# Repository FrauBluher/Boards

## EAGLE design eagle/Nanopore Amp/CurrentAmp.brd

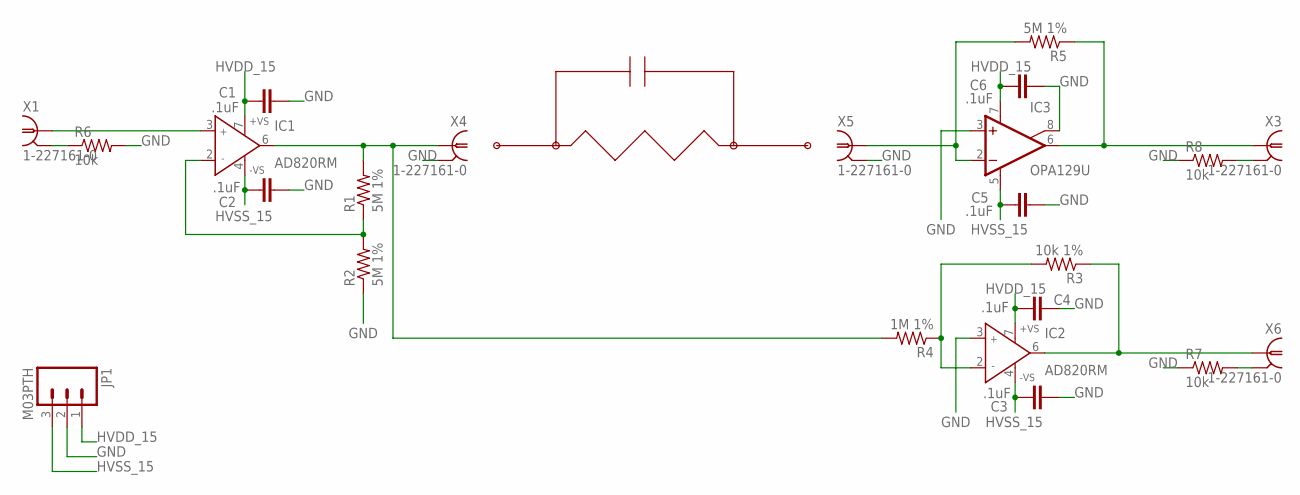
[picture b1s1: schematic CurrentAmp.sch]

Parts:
C1, C2, C3, C4, C5, C6: .1uF; 0805
IC1, IC2: AD820RM; MSOP08
IC3: OPA129U; SO08
JP1: M03PTH; 1X03
R1, R2, R5: 5M 1%; 0805
R3: 10k 1%; 0805
R4: 1M 1%; 0805
R6, R7, R8: 10k; 0805
X1, X3, X4, X5, X6: 1-227161-0; AMP_227161

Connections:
GND: C1.2, C2.2, C3.2, C4.2, C5.2, C6.2, IC2.3 (IN+), IC3.3 (+IN), IC3.8 (SUBS), JP1.2, R2.1, R6.2, R7.1, R8.1, X4.2, X5.2
HVDD_15: C1.1, C4.1, C6.1, IC1.7 (+VS), IC2.7 (+VS), IC3.7 (V+), JP1.1
HVSS_15: C2.1, C3.1, C5.1, IC1.4 (-VS), IC2.4 (-VS), IC3.5 (V-), JP1.3
unnamed: IC1.2 (IN-), R1.1, R2.2
unnamed: IC1.3 (IN+), X1.1
unnamed: IC2.2 (IN-), R3.2, R4.1
unnamed: IC2.6 (OUT), R3.1, X6.1
unnamed: IC1.6 (OUT), R1.2, R4.2, X4.1
unnamed: IC3.6 (OUT), R5.1, X3.1
unnamed: IC3.2 (-IN), R5.2, X5.1
unnamed: R6.1, X1.2
unnamed: R8.2, X3.2
unnamed: R7.2, X6.2

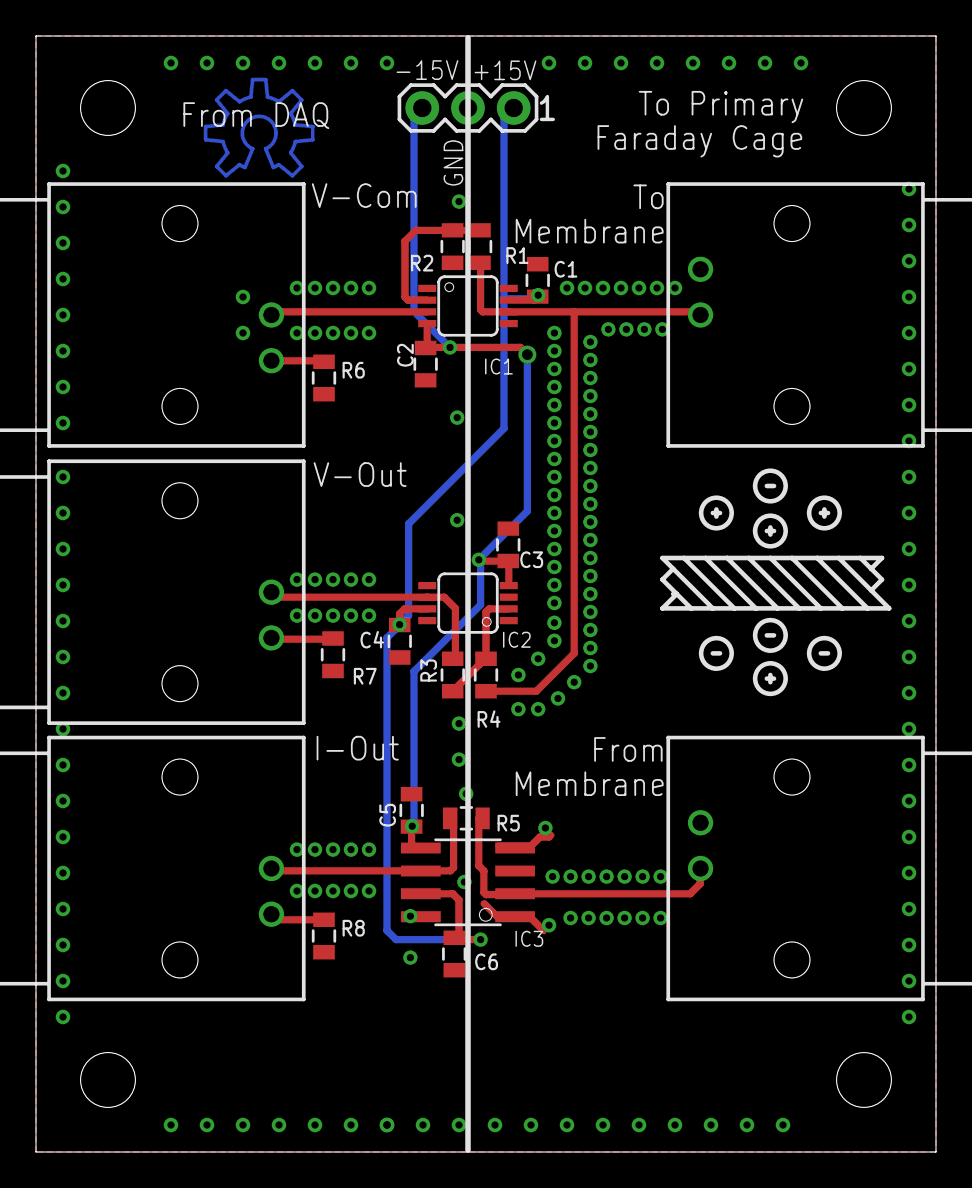
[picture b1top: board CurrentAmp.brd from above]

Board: 2 copper layers, 50.0 x 62.0 mm, 27 parts (0 on the bottom side), 13 nets.

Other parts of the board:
E$1, E$2, E$3, E$4: STAND-OFF-TIGHT

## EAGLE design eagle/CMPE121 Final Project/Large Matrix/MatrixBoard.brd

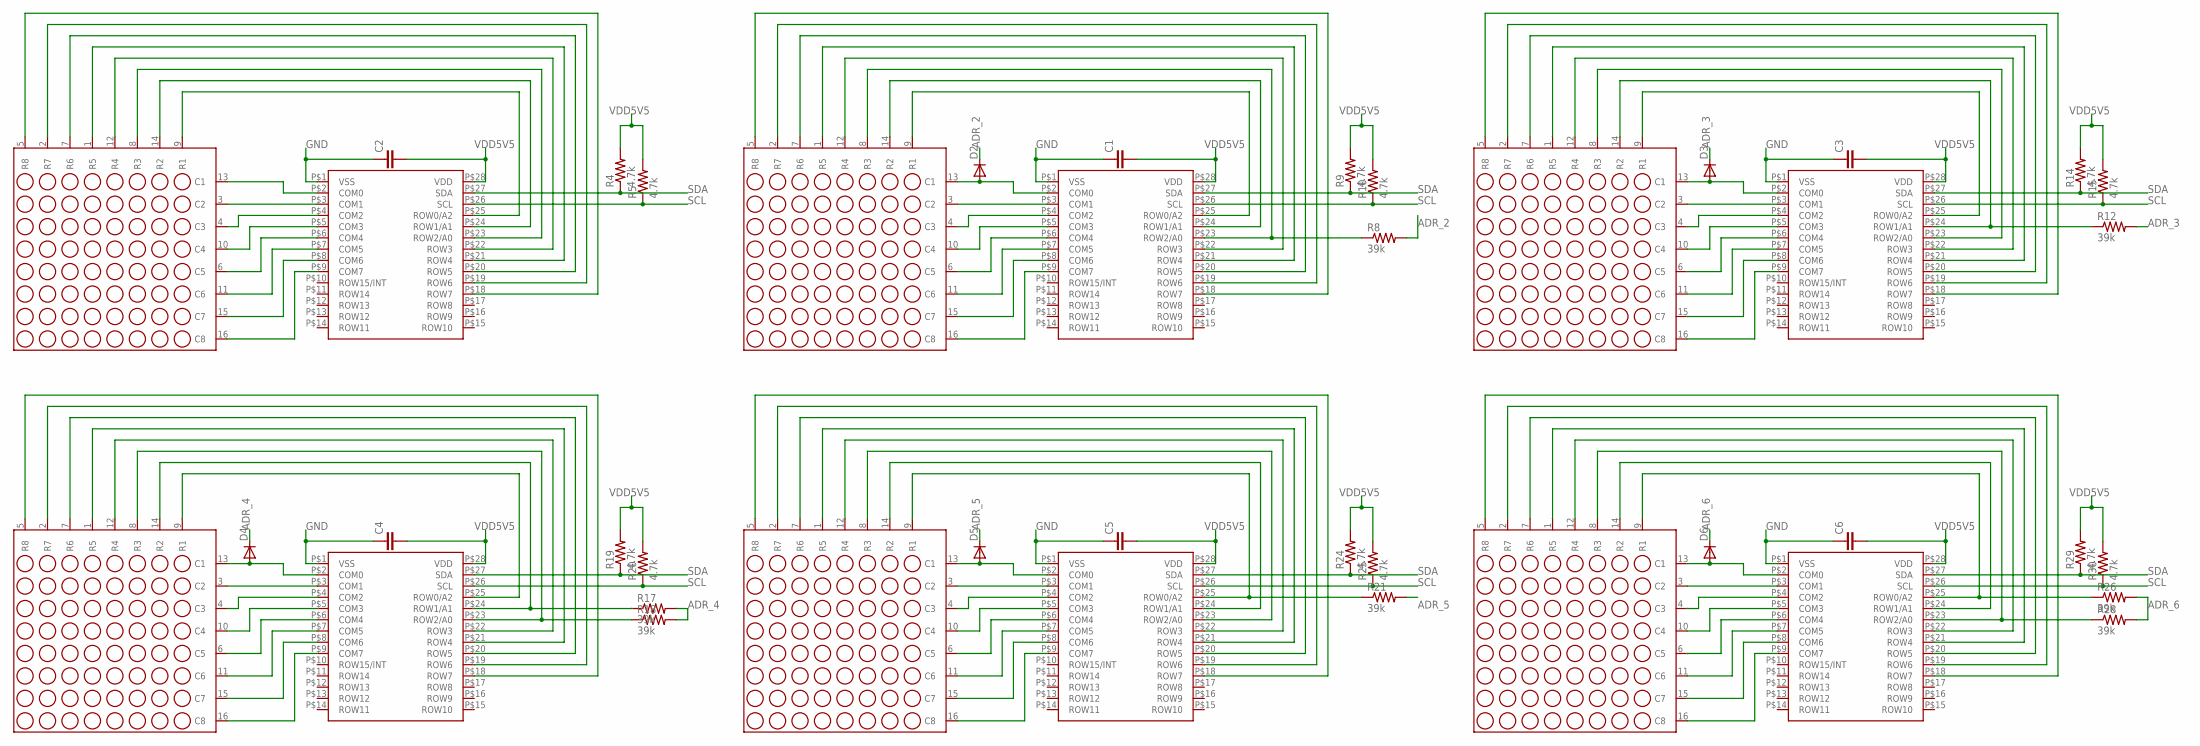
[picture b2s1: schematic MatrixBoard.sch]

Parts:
C1, C2, C3, C4, C5, C6: CAP0805; 0805
D2, D3, D4, D5, D6: DIODESMA; SMA-DIODE
R4, R5, R9, R10, R14, R15, R19, R20, R24, R25, R29, R30: 4.7k; 0805
R8, R12, R17, R18, R21, R26, R28: 39k; 0805
U$2, U$4, U$6, U$8, U$10, U$12: A-788BS
U$3, U$5, U$7, U$9, U$11, U$13: HT16K33; SOIC28-W

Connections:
ADR_2: D2.C, R8.2
ADR_3: D3.C, R12.2
ADR_4: D4.C, R17.2, R18.2
ADR_5: D5.C, R21.2
ADR_6: D6.C, R26.2, R28.2
GND: C1.1, C2.1, C3.1, C4.1, C5.1, C6.1, U$3.P$1 (VSS), U$5.P$1 (VSS), U$7.P$1 (VSS), U$9.P$1 (VSS), U$11.P$1 (VSS), U$13.P$1 (VSS)
unnamed: U$2.13 (C1), U$3.P$2 (COM0)
unnamed: U$2.3 (C2), U$3.P$3 (COM1)
unnamed: U$2.4 (C3), U$3.P$4 (COM2)
unnamed: U$2.10 (C4), U$3.P$5 (COM3)
unnamed: U$2.6 (C5), U$3.P$6 (COM4)
unnamed: U$2.11 (C6), U$3.P$7 (COM5)
unnamed: U$2.15 (C7), U$3.P$8 (COM6)
unnamed: U$2.16 (C8), U$3.P$9 (COM7)
unnamed: D2.A, U$4.13 (C1), U$5.P$2 (COM0)
unnamed: U$4.3 (C2), U$5.P$3 (COM1)
unnamed: U$4.4 (C3), U$5.P$4 (COM2)
unnamed: U$4.10 (C4), U$5.P$5 (COM3)
unnamed: U$2.9 (R1), U$3.P$25 (ROW0/A2)
unnamed: U$2.14 (R2), U$3.P$24 (ROW1/A1)
unnamed: U$2.8 (R3), U$3.P$23 (ROW2/A0)
unnamed: U$2.12 (R4), U$3.P$22 (ROW3)
unnamed: U$2.1 (R5), U$3.P$21 (ROW4)
unnamed: U$2.7 (R6), U$3.P$20 (ROW5)
unnamed: U$2.2 (R7), U$3.P$19 (ROW6)
unnamed: U$2.5 (R8), U$3.P$18 (ROW7)
unnamed: U$4.6 (C5), U$5.P$6 (COM4)
unnamed: U$4.11 (C6), U$5.P$7 (COM5)
unnamed: U$4.15 (C7), U$5.P$8 (COM6)
unnamed: U$4.16 (C8), U$5.P$9 (COM7)
unnamed: U$4.9 (R1), U$5.P$25 (ROW0/A2)
unnamed: U$4.14 (R2), U$5.P$24 (ROW1/A1)
unnamed: R8.1, U$4.8 (R3), U$5.P$23 (ROW2/A0)
unnamed: U$4.12 (R4), U$5.P$22 (ROW3)
unnamed: U$4.1 (R5), U$5.P$21 (ROW4)
unnamed: U$4.7 (R6), U$5.P$20 (ROW5)
unnamed: U$4.2 (R7), U$5.P$19 (ROW6)
unnamed: U$4.5 (R8), U$5.P$18 (ROW7)
unnamed: D3.A, U$6.13 (C1), U$7.P$2 (COM0)
unnamed: U$6.3 (C2), U$7.P$3 (COM1)
unnamed: U$6.4 (C3), U$7.P$4 (COM2)
unnamed: U$6.10 (C4), U$7.P$5 (COM3)
unnamed: U$6.6 (C5), U$7.P$6 (COM4)
unnamed: U$6.11 (C6), U$7.P$7 (COM5)
unnamed: U$6.15 (C7), U$7.P$8 (COM6)
unnamed: U$6.16 (C8), U$7.P$9 (COM7)
unnamed: U$6.9 (R1), U$7.P$25 (ROW0/A2)
unnamed: R12.1, U$6.14 (R2), U$7.P$24 (ROW1/A1)
unnamed: U$6.8 (R3), U$7.P$23 (ROW2/A0)
unnamed: U$6.12 (R4), U$7.P$22 (ROW3)
unnamed: U$6.1 (R5), U$7.P$21 (ROW4)
unnamed: U$6.7 (R6), U$7.P$20 (ROW5)
unnamed: U$6.2 (R7), U$7.P$19 (ROW6)
unnamed: U$6.5 (R8), U$7.P$18 (ROW7)
unnamed: D4.A, U$12.13 (C1), U$13.P$2 (COM0)
unnamed: U$12.3 (C2), U$13.P$3 (COM1)
unnamed: U$12.4 (C3), U$13.P$4 (COM2)
unnamed: U$12.10 (C4), U$13.P$5 (COM3)
unnamed: U$12.6 (C5), U$13.P$6 (COM4)
unnamed: U$12.11 (C6), U$13.P$7 (COM5)
unnamed: U$12.15 (C7), U$13.P$8 (COM6)
unnamed: U$12.16 (C8), U$13.P$9 (COM7)
unnamed: U$12.9 (R1), U$13.P$25 (ROW0/A2)
unnamed: R17.1, U$12.14 (R2), U$13.P$24 (ROW1/A1)
unnamed: R18.1, U$12.8 (R3), U$13.P$23 (ROW2/A0)
unnamed: U$12.12 (R4), U$13.P$22 (ROW3)
unnamed: U$12.1 (R5), U$13.P$21 (ROW4)
unnamed: U$12.7 (R6), U$13.P$20 (ROW5)
unnamed: U$12.2 (R7), U$13.P$19 (ROW6)
unnamed: U$12.5 (R8), U$13.P$18 (ROW7)
unnamed: D5.A, U$10.13 (C1), U$11.P$2 (COM0)
unnamed: U$10.3 (C2), U$11.P$3 (COM1)
unnamed: U$10.4 (C3), U$11.P$4 (COM2)
unnamed: U$10.10 (C4), U$11.P$5 (COM3)
unnamed: U$10.6 (C5), U$11.P$6 (COM4)
unnamed: U$10.11 (C6), U$11.P$7 (COM5)
unnamed: U$10.15 (C7), U$11.P$8 (COM6)
unnamed: U$10.16 (C8), U$11.P$9 (COM7)
unnamed: R21.1, U$10.9 (R1), U$11.P$25 (ROW0/A2)
unnamed: U$10.14 (R2), U$11.P$24 (ROW1/A1)
unnamed: U$10.8 (R3), U$11.P$23 (ROW2/A0)
unnamed: U$10.12 (R4), U$11.P$22 (ROW3)
unnamed: U$10.1 (R5), U$11.P$21 (ROW4)
unnamed: U$10.7 (R6), U$11.P$20 (ROW5)
unnamed: U$10.2 (R7), U$11.P$19 (ROW6)
unnamed: U$10.5 (R8), U$11.P$18 (ROW7)
unnamed: D6.A, U$8.13 (C1), U$9.P$2 (COM0)
unnamed: U$8.3 (C2), U$9.P$3 (COM1)
unnamed: U$8.4 (C3), U$9.P$4 (COM2)
unnamed: U$8.10 (C4), U$9.P$5 (COM3)
unnamed: U$8.6 (C5), U$9.P$6 (COM4)
unnamed: U$8.11 (C6), U$9.P$7 (COM5)
unnamed: U$8.15 (C7), U$9.P$8 (COM6)
unnamed: U$8.16 (C8), U$9.P$9 (COM7)
unnamed: R26.1, U$8.9 (R1), U$9.P$25 (ROW0/A2)
unnamed: U$8.14 (R2), U$9.P$24 (ROW1/A1)
unnamed: R28.1, U$8.8 (R3), U$9.P$23 (ROW2/A0)
unnamed: U$8.12 (R4), U$9.P$22 (ROW3)
unnamed: U$8.1 (R5), U$9.P$21 (ROW4)
unnamed: U$8.7 (R6), U$9.P$20 (ROW5)
unnamed: U$8.2 (R7), U$9.P$19 (ROW6)
unnamed: U$8.5 (R8), U$9.P$18 (ROW7)
SCL: R5.1, R10.1, R15.1, R20.1, R25.1, R30.1, U$3.P$26 (SCL), U$5.P$26 (SCL), U$7.P$26 (SCL), U$9.P$26 (SCL), U$11.P$26 (SCL), U$13.P$26 (SCL)
SDA: R4.1, R9.1, R14.1, R19.1, R24.1, R29.1, U$3.P$27 (SDA), U$5.P$27 (SDA), U$7.P$27 (SDA), U$9.P$27 (SDA), U$11.P$27 (SDA), U$13.P$27 (SDA)
VDD5V5: C1.2, C2.2, C3.2, C4.2, C5.2, C6.2, R4.2, R5.2, R9.2, R10.2, R14.2, R15.2, R19.2, R20.2, R24.2, R25.2, R29.2, R30.2, U$3.P$28 (VDD), U$5.P$28 (VDD), U$7.P$28 (VDD), U$9.P$28 (VDD), U$11.P$28 (VDD), U$13.P$28 (VDD)

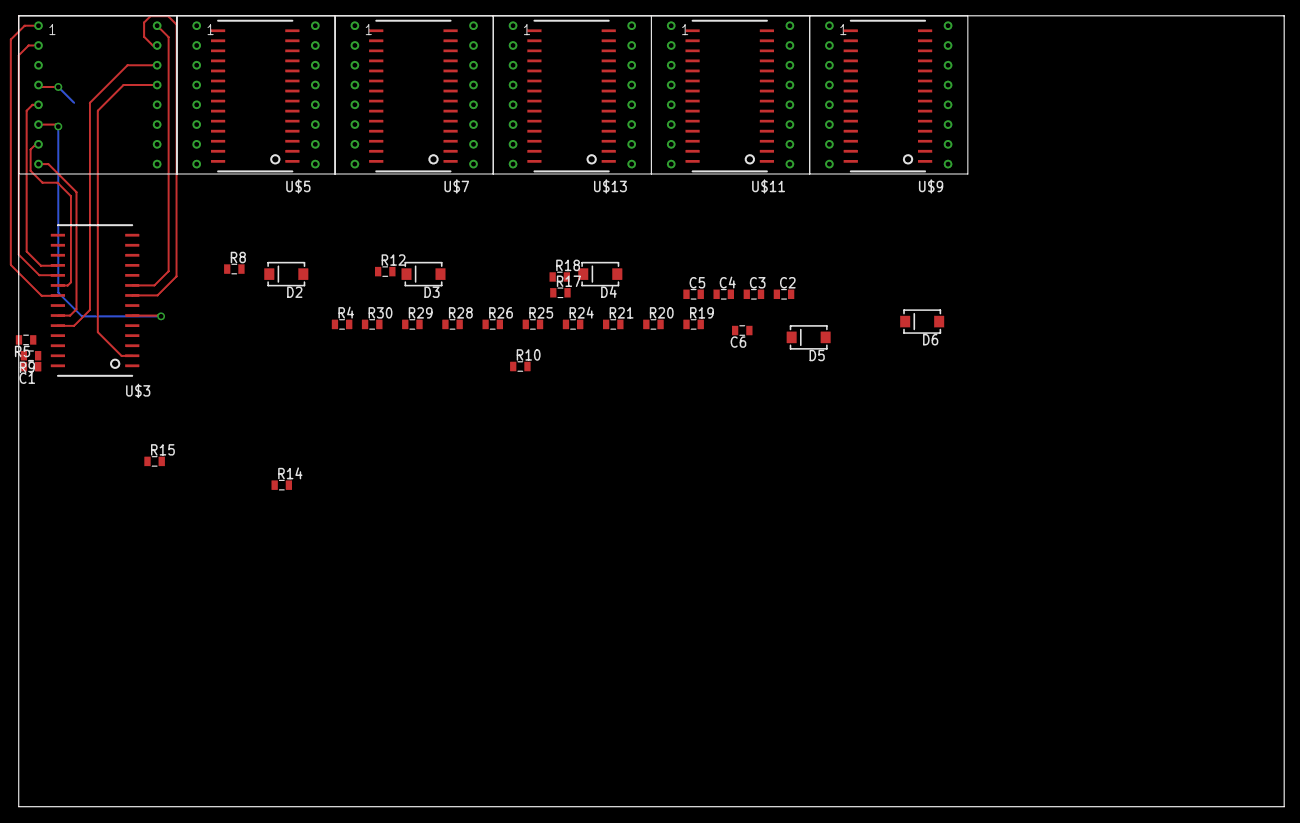
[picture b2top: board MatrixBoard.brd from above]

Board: 2 copper layers, 160.0 x 100.0 mm, 42 parts (0 on the bottom side), 105 nets.

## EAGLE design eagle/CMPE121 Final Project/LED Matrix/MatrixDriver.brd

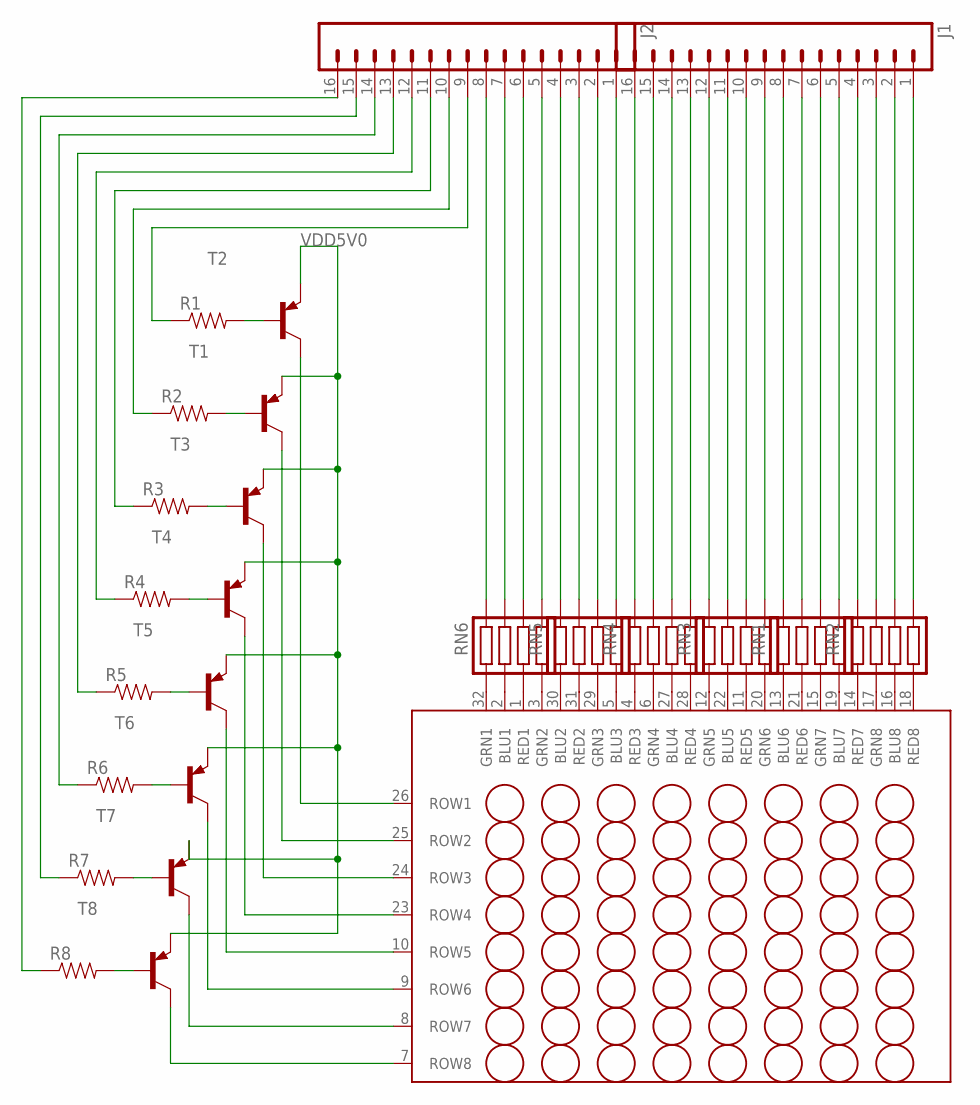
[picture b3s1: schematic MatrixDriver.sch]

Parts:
J1, J2: M16DUAL_ROW; 2X8
R1, R2, R3, R4, R5, R6, R7, R8: RESISTOR0805-RES; 0805
RN1, RN2, RN3, RN4, RN5, RN6: RESISTOR_ARRAY-4; EXB-38V271JV
T1, T2, T3, T4, T5, T6, T7, T8: 2N3906-PNP-TO92-EBC; TO92-EBC
U$1: BL-M23B88RGB-11; 8X8RGBMATRIX

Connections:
unnamed: T2.C, U$1.26 (ROW1)
unnamed: T1.C, U$1.25 (ROW2)
unnamed: T3.C, U$1.24 (ROW3)
unnamed: T4.C, U$1.23 (ROW4)
unnamed: T5.C, U$1.10 (ROW5)
unnamed: T6.C, U$1.9 (ROW6)
unnamed: T7.C, U$1.8 (ROW7)
unnamed: T8.C, U$1.7 (ROW8)
unnamed: RN1.P$5 (5), U$1.19 (BLU7)
unnamed: RN1.P$6 (6), U$1.15 (GRN7)
unnamed: RN1.P$7 (7), U$1.21 (RED6)
unnamed: RN1.P$8 (8), U$1.13 (BLU6)
unnamed: RN2.P$5 (5), U$1.18 (RED8)
unnamed: RN2.P$6 (6), U$1.16 (BLU8)
unnamed: RN2.P$7 (7), U$1.17 (GRN8)
unnamed: RN2.P$8 (8), U$1.14 (RED7)
unnamed: RN3.P$5 (5), U$1.20 (GRN6)
unnamed: RN3.P$6 (6), U$1.11 (RED5)
unnamed: RN3.P$7 (7), U$1.22 (BLU5)
unnamed: RN3.P$8 (8), U$1.12 (GRN5)
unnamed: RN4.P$5 (5), U$1.28 (RED4)
unnamed: RN4.P$6 (6), U$1.27 (BLU4)
unnamed: RN4.P$7 (7), U$1.6 (GRN4)
unnamed: RN4.P$8 (8), U$1.4 (RED3)
unnamed: RN5.P$5 (5), U$1.5 (BLU3)
unnamed: RN5.P$6 (6), U$1.29 (GRN3)
unnamed: RN5.P$7 (7), U$1.31 (RED2)
unnamed: RN5.P$8 (8), U$1.30 (BLU2)
unnamed: RN6.P$5 (5), U$1.3 (GRN2)
unnamed: RN6.P$6 (6), U$1.1 (RED1)
unnamed: RN6.P$7 (7), U$1.2 (BLU1)
unnamed: RN6.P$8 (8), U$1.32 (GRN1)
unnamed: J1.13, RN4.P$4 (4)
unnamed: J1.14, RN4.P$3 (3)
unnamed: J1.15, RN4.P$2 (2)
unnamed: J1.16, RN4.P$1 (1)
unnamed: J1.9, RN3.P$4 (4)
unnamed: J1.10, RN3.P$3 (3)
unnamed: J1.11, RN3.P$2 (2)
unnamed: J1.12, RN3.P$1 (1)
unnamed: J1.5, RN1.P$4 (4)
unnamed: J1.6, RN1.P$3 (3)
unnamed: J1.7, RN1.P$2 (2)
unnamed: J1.8, RN1.P$1 (1)
unnamed: J1.1, RN2.P$4 (4)
unnamed: J1.2, RN2.P$3 (3)
unnamed: J1.3, RN2.P$2 (2)
unnamed: J1.4, RN2.P$1 (1)
unnamed: J2.5, RN6.P$4 (4)
unnamed: J2.6, RN6.P$3 (3)
unnamed: J2.7, RN6.P$2 (2)
unnamed: J2.8, RN6.P$1 (1)
unnamed: J2.1, RN5.P$4 (4)
unnamed: J2.2, RN5.P$3 (3)
unnamed: J2.3, RN5.P$2 (2)
unnamed: J2.4, RN5.P$1 (1)
unnamed: J2.9, R1.1
unnamed: J2.10, R2.1
unnamed: J2.11, R3.1
unnamed: J2.12, R4.1
unnamed: J2.13, R5.1
unnamed: J2.14, R6.1
unnamed: J2.15, R7.1
unnamed: J2.16, R8.1
ROW1: R1.2, T2.B
ROW2: R2.2, T1.B
ROW3: R3.2, T3.B
ROW4: R4.2, T4.B
ROW5: R5.2, T5.B
ROW6: R6.2, T6.B
ROW7: R7.2, T7.B
ROW8: R8.2, T8.B
VDD5V0: T1.E, T2.E, T3.E, T4.E, T5.E, T6.E, T7.E, T8.E

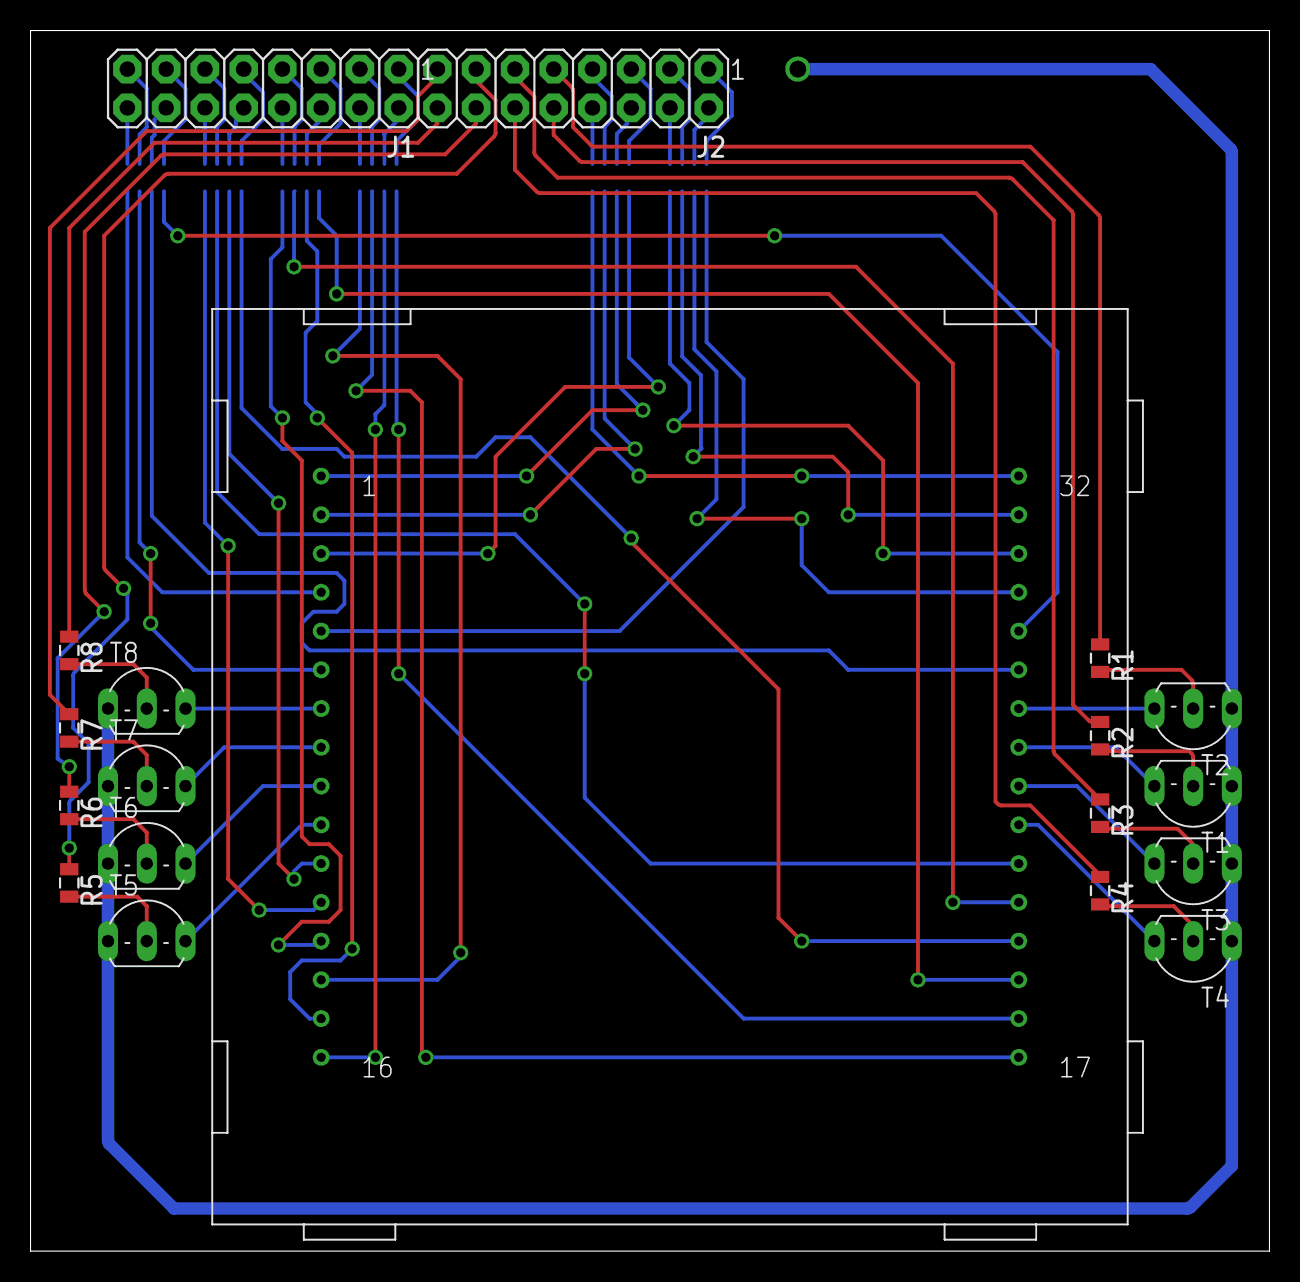
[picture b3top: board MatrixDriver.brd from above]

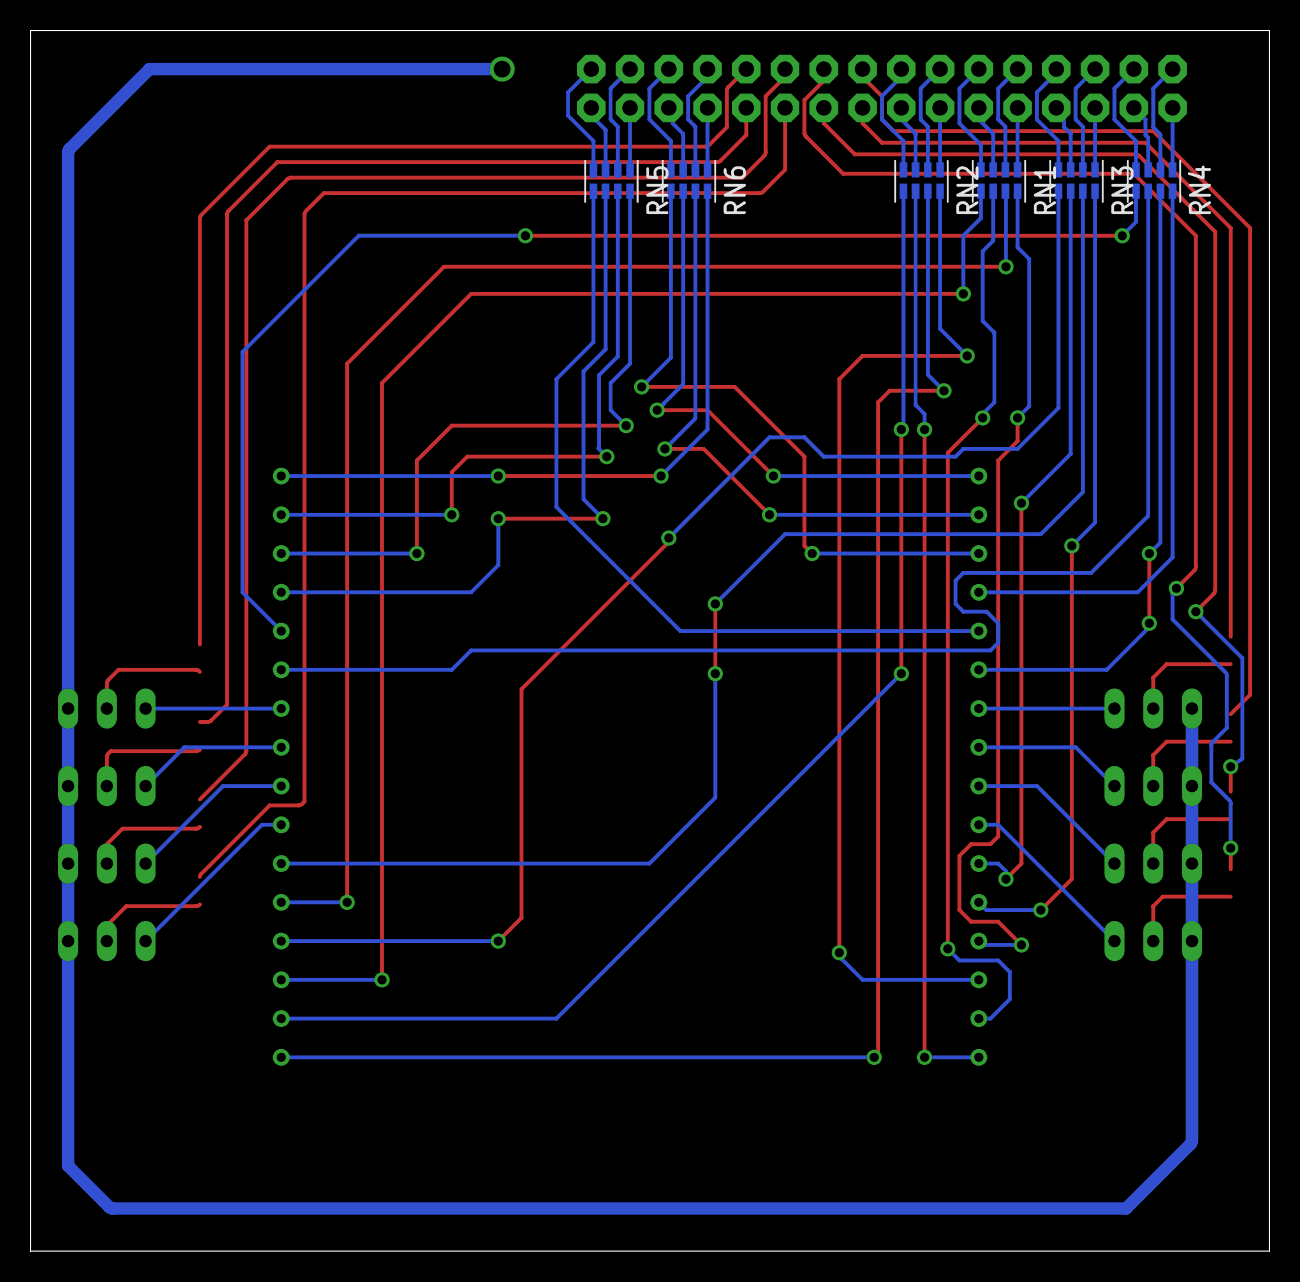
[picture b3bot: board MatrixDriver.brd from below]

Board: 2 copper layers, 81.2 x 80.0 mm, 25 parts (6 on the bottom side), 73 nets.

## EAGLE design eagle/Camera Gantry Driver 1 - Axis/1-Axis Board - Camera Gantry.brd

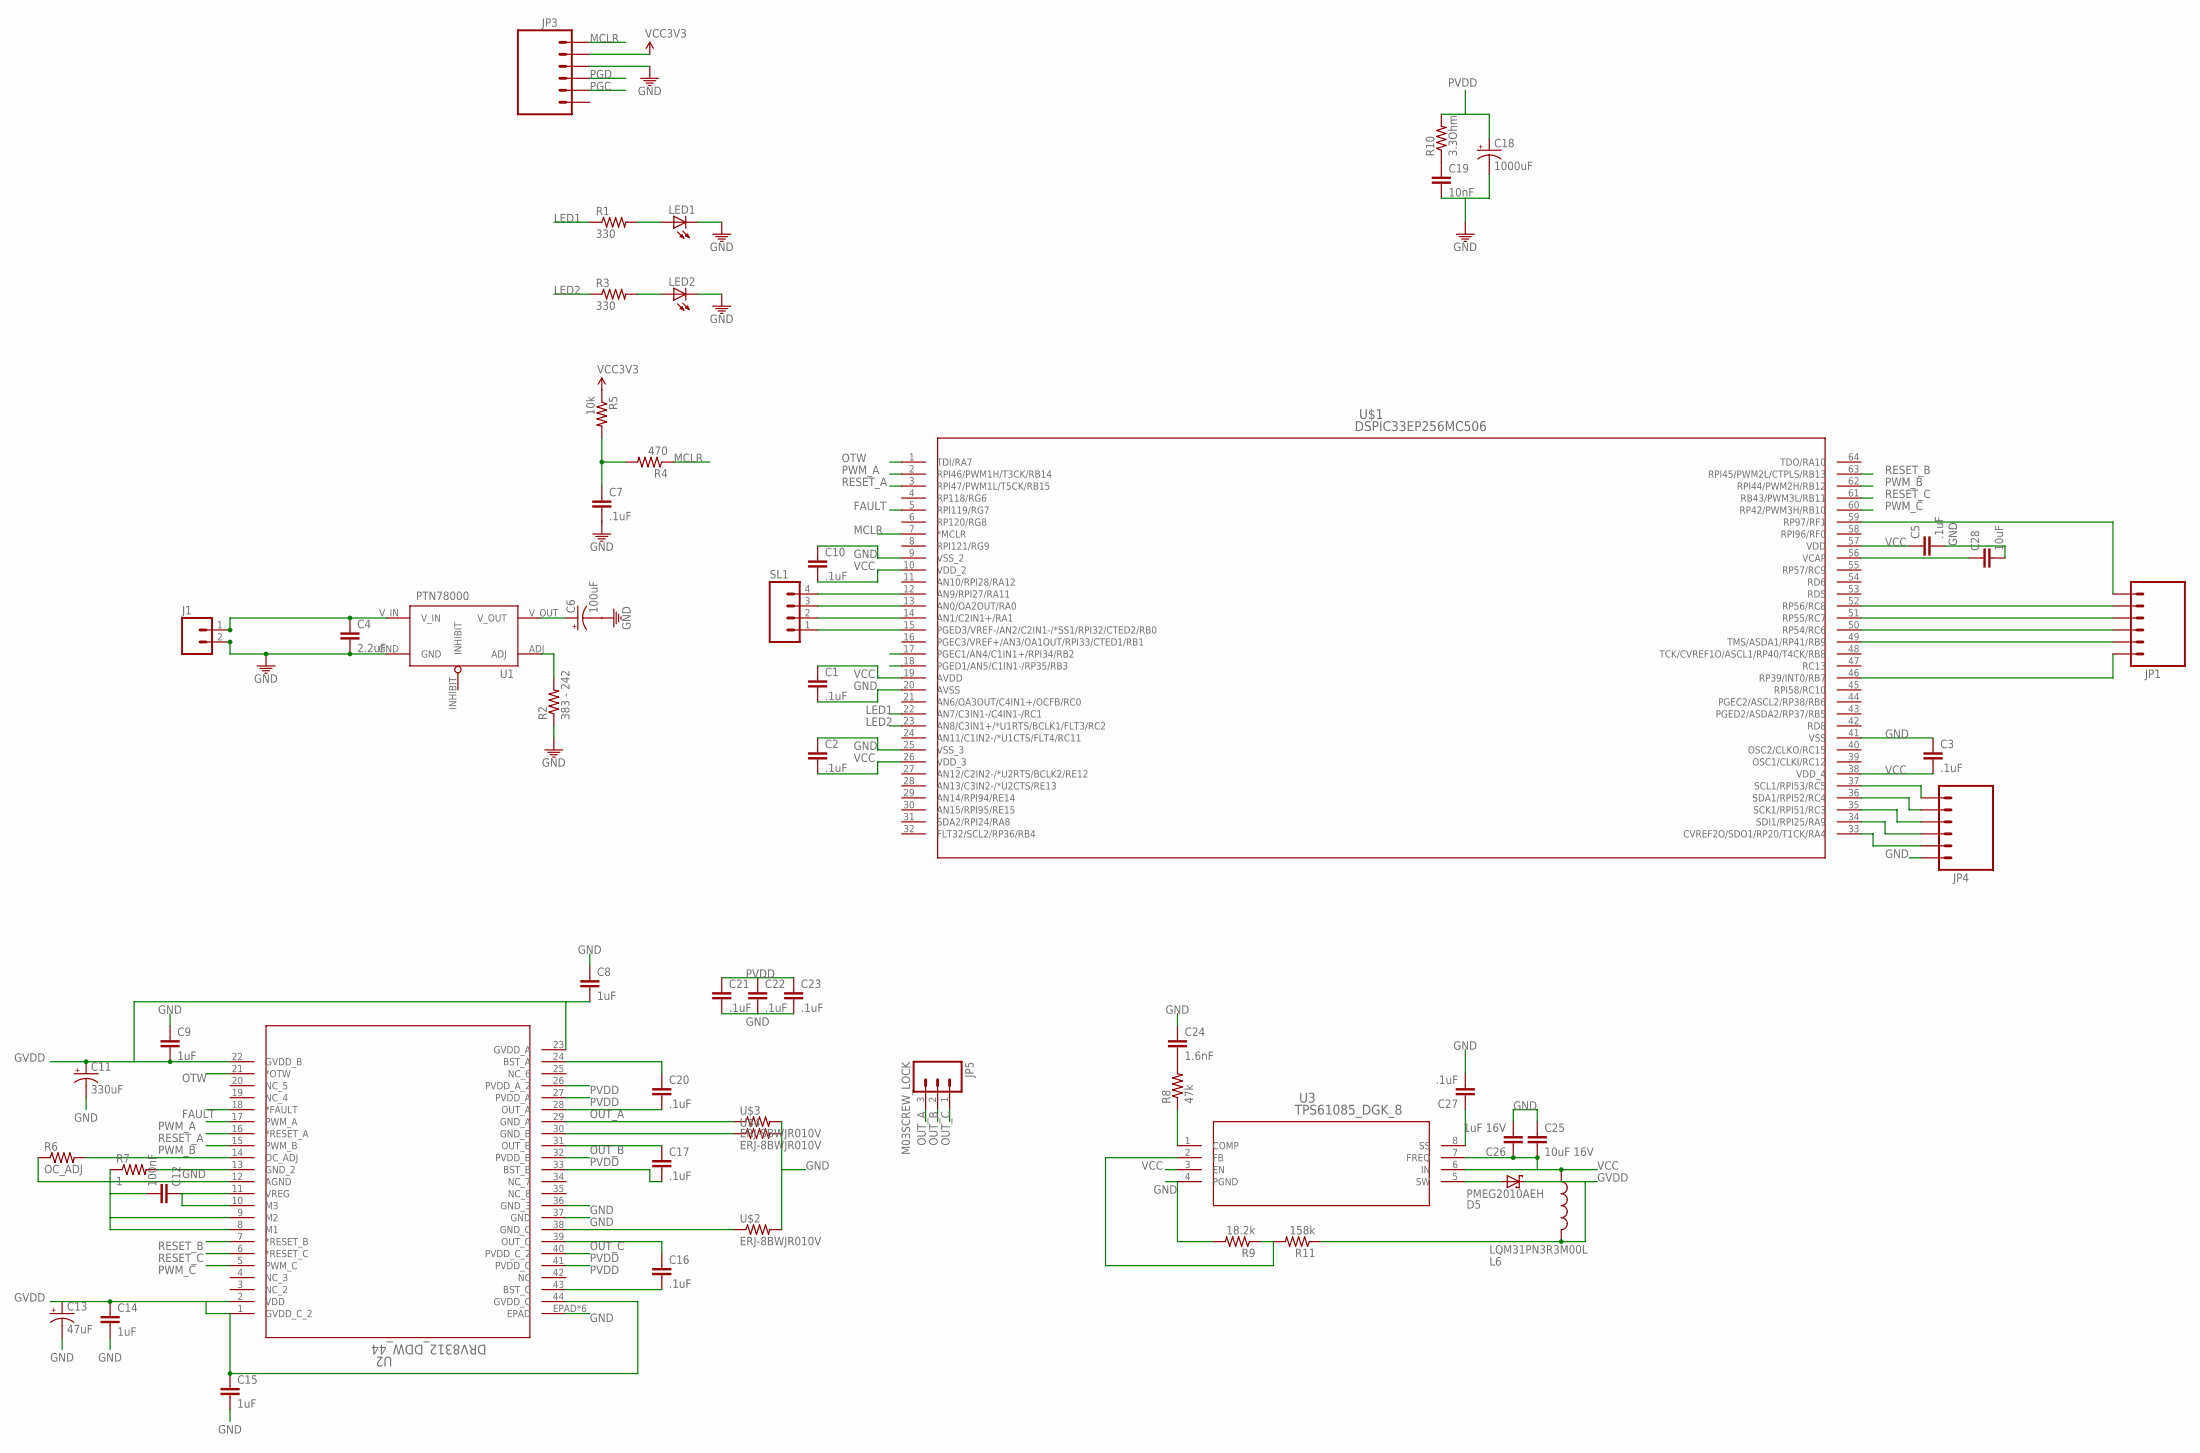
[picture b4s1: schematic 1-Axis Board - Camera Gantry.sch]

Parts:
C1, C2, C3, C5, C7, C10, C16, C17, C20, C21, C22, C23, C27: .1uF; 0805
C4: 2.2uF; 1206
C6: 100uF; CPOL-RADIAL-100UF-25V
C8, C9, C14, C15: 1uF; 0805
C11: 330uF; CPOL-RADIAL-1000UF-25V
C12: 100nF; 0805
C13: 47uF; CPOL-RADIAL-1000UF-25V
C18: 1000uF; CPOL-RADIAL-1000UF-25V
C19: 10nF; 0805
C24: 1.6nF; 0805
C25: 10uF 16V; 1206
C26: 1uF 16V; 0805
C28: 10uF; 1206
D5: PMEG2010AEH; SOD-123
J1: M023.5MM-NO_SILK; SCREWTERMINAL-3.5MM-2-NS
JP1, JP3, JP4: M06LOCK; 1X06_LOCK
JP5: M03SCREW_LOCK; SCREWTERMINAL-3.5MM-3_LOCK.007S
L6: LQM31PN3R3M00L; 1206
LED1, LED2: LED1206; LED-1206
R1, R3: 330; 0805
R2: 383 - 242; 0805
R4: 470; 0805
R5: 10k; 0805
R6: OC_ADJ; 0805
R7: 1; 0805
R8: 47k; 0805
R9: 18.2k; 0805
R10: 3.3Ohm; 0805
R11: 158k; 0805
SL1: M04LOCK; 1X04_LOCK
U1: PTN78000
U2: DRV8312_DDW_44; DDW44_8P26X4P31
U3: TPS61085_DGK_8; DGK8
U$1: DSPIC33EP256MC506; QFP64-10X10MC
U$2, U$3, U$4: ERJ-8BWJR010V; 1206

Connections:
FAULT: U2.18 (*FAULT), U$1.5 (RPI119/RG7)
GND: C1.2, C2.1, C3.1, C4.2, C5.2, C6.2 (-), C7.2, C8.1, C9.1, C10.1, C11.2 (-), C13.2 (-), C14.2, C15.2, C18.2 (-), C19.2, C21.2, C22.2, C23.2, C24.1, C25.1, C26.2, C27.2, C28.2, J1.2 (1), JP3.3, JP4.1, LED1.C, LED2.C, R2.1, R7.2, R9.2, U1.GND, U2.13 (GND_2), U2.36 (GND_3), U2.37 (GND), U2.EPAD, U2.P$1 (EPAD), U2.P$2 (EPAD), U2.P$3 (EPAD), U2.P$7 (EPAD), U2.P$8 (EPAD), U3.4 (PGND), U$1.9 (VSS_2), U$1.20 (AVSS), U$1.25 (VSS_3), U$1.41 (VSS), U$2.2, U$3.2, U$4.2
GVDD: C8.2, C9.2, C11.1 (+), C13.1 (+), C14.1, C15.1, D5.C, L6.2, R11.1, U2.1 (GVDD_C_2), U2.2 (VDD), U2.22 (GVDD_B), U2.23 (GVDD_A), U2.44 (GVDD_C)
LED1: R1.1, U$1.22 (AN7/C3IN1-/C4IN1-/RC1)
LED2: R3.1, U$1.23 (AN8/C3IN1+/*U1RTS/BCLK1/FLT3/RC2)
MCLR: JP3.1, R4.1, U$1.7 (*MCLR)
unnamed: LED1.A, R1.2
unnamed: C7.1, R4.2, R5.2
unnamed: LED2.A, R3.2
unnamed: U2.38 (GND_C), U$2.1
unnamed: U2.29 (GND_A), U$3.1
unnamed: R2.2, U1.ADJ
unnamed: U2.30 (GND_B), U$4.1
unnamed: C27.1, U3.8 (SS)
unnamed: R8.1, U3.1 (COMP)
unnamed: C24.2, R8.2
unnamed: C19.1, R10.1
unnamed: C28.1, U$1.56 (VCAP)
unnamed: D5.A, U3.5 (SW)
unnamed: R9.1, R11.2, U3.2 (FB)
unnamed: C16.2, U2.43 (BST_C)
unnamed: JP1.1, U$1.46 (RP39/INT0/RB7)
unnamed: JP1.2, U$1.49 (TMS/ASDA1/RP41/RB9)
unnamed: JP1.3, U$1.50 (RP54/RC6)
unnamed: JP1.5, U$1.52 (RP56/RC8)
unnamed: JP1.6, U$1.59 (RP97/RF1)
unnamed: C17.2, U2.33 (BST_B)
unnamed: JP1.4, U$1.51 (RP55/RC7)
unnamed: JP4.4, U$1.35 (SCK1/RPI51/RC3)
unnamed: JP4.5, U$1.36 (SDA1/RPI52/RC4)
unnamed: JP4.6, U$1.37 (SCL1/RPI53/RC5)
unnamed: JP4.3, U$1.34 (SDI1/RPI25/RA9)
unnamed: C20.1, U2.24 (BST_A)
unnamed: SL1.1, U$1.15 (PGED3/VREF-/AN2/C2IN1-/*SS1/RPI32/CTED2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)
unnamed: SL1.2, U$1.14 (AN1/C2IN1+/RA1)
unnamed: SL1.3, U$1.13 (AN0/OA2OUT/RA0)
unnamed: SL1.4, U$1.12 (AN9/RPI27/RA11)
unnamed: JP4.2, U$1.33 (CVREF2O/SDO1/RP20/T1CK/RA4)
unnamed: C12.2, R6.1, R7.1, U2.8 (M1), U2.9 (M2), U2.12 (AGND)
unnamed: C12.1, U2.10 (M3), U2.11 (VREG)
OC_ADJ: R6.2, U2.14 (OC_ADJ)
OTW: U2.21 (*OTW), U$1.1 (TDI/RA7)
OUT_A: C20.2, JP5.3, U2.28 (OUT_A)
OUT_B: C17.1, JP5.2, U2.31 (OUT_B)
OUT_C: C16.1, JP5.1, U2.39 (OUT_C)
PGC: JP3.5, U$1.17 (PGEC1/AN4/C1IN1+/RPI34/RB2)
PGD: JP3.4, U$1.18 (PGED1/AN5/C1IN1-/RP35/RB3)
PVDD: C4.1, C18.1 (+), C21.1, C22.1, C23.1, J1.1 (2), R10.2, U1.V_IN, U2.26 (PVDD_A_2), U2.27 (PVDD_A), U2.32 (PVDD_B), U2.40 (PVDD_C_2), U2.41 (PVDD_C)
PWM_A: U2.17 (PWM_A), U$1.2 (RPI46/PWM1H/T3CK/RB14)
PWM_B: U2.15 (PWM_B), U$1.62 (RPI44/PWM2H/RB12)
PWM_C: U2.5 (PWM_C), U$1.60 (RP42/PWM3H/RB10)
RESET_A: U2.16 (*RESET_A), U$1.3 (RPI47/PWM1L/T5CK/RB15)
RESET_B: U2.7 (*RESET_B), U$1.63 (RPI45/PWM2L/CTPLS/RB13)
RESET_C: U2.6 (*RESET_C), U$1.61 (RB43/PWM3L/RB11)
VCC: C1.1, C2.2, C3.2, C5.1, C6.1 (+), C10.2, C25.2, C26.1, L6.1, U1.V_OUT, U3.3 (EN), U3.6 (IN), U3.7 (FREQ), U$1.10 (VDD_2), U$1.19 (AVDD), U$1.26 (VDD_3), U$1.38 (VDD_4), U$1.57 (VDD)
VCC3V3: JP3.2, R5.1

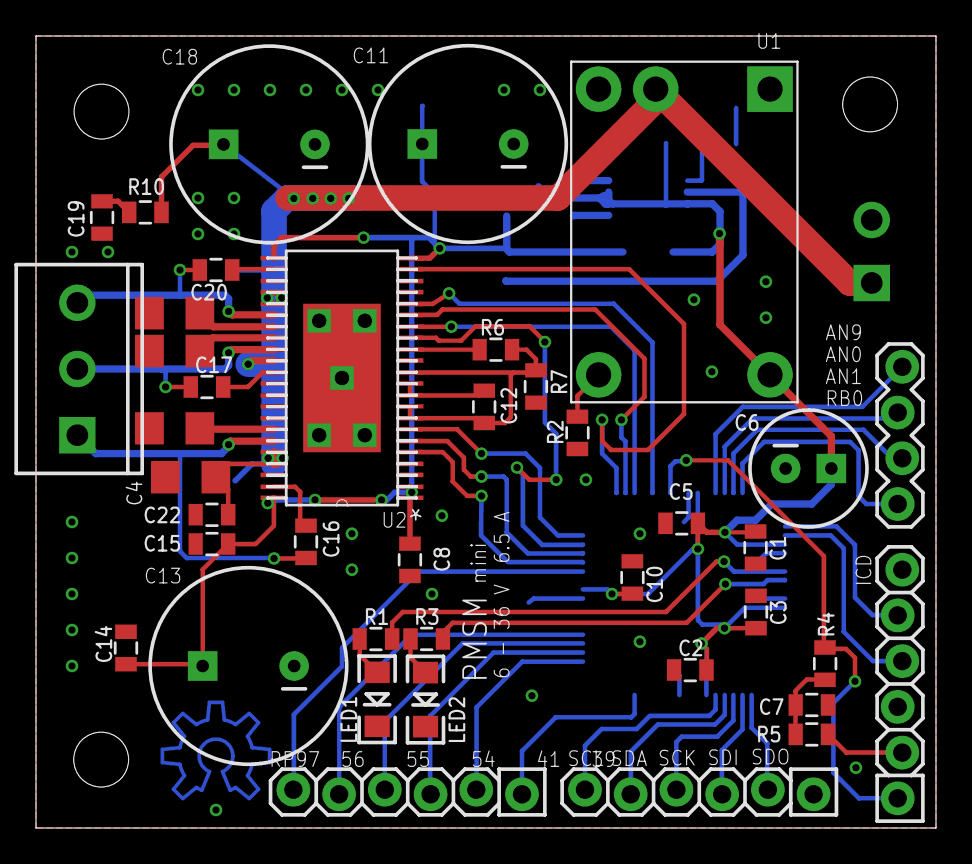
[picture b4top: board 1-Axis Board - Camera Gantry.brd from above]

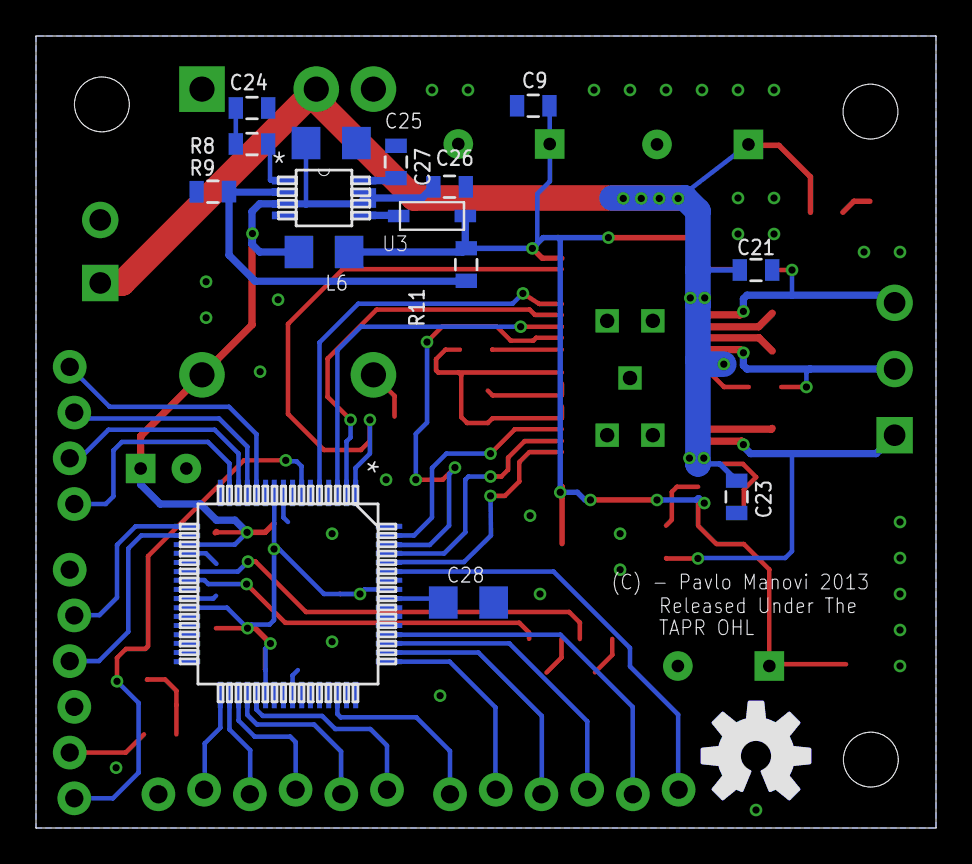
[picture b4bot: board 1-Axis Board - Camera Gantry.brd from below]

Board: 2 copper layers, 50.0 x 44.0 mm, 59 parts (15 on the bottom side), 56 nets.

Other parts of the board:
E$1, E$3, E$4: STAND-OFF-TIGHT

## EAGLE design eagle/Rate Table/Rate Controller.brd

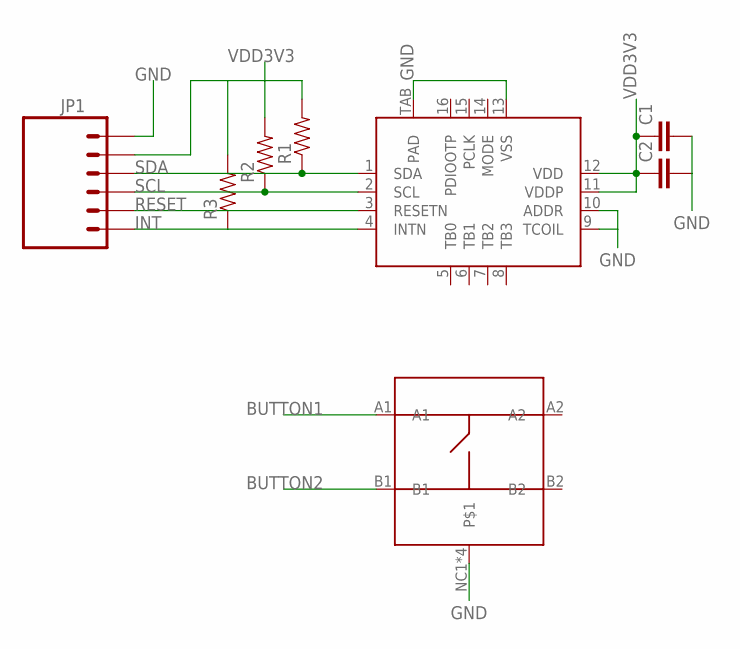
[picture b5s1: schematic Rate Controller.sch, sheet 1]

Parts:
C1, C2: CAP0805; 0805
JP1: M06DUAL_ROW; 2X03
R1, R2, R3: RESISTOR0805-RES; 0805
U$1: N50P105
U$2: AC5013; QFN16

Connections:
BUTTON1: U$1.A1
BUTTON2: U$1.B1
GND: C1.2, C2.2, JP1.1, U$1.NC1, U$1.NC2, U$1.NC3, U$1.NC4, U$2.9 (TCOIL), U$2.10 (ADDR), U$2.13 (VSS), U$2.TAB (PAD)
INT: JP1.6, R3.1, U$2.4 (INTN)
RESET: JP1.5, U$2.3 (RESETN)
SCL: JP1.4, R2.1, U$2.2 (SCL)
SDA: JP1.3, R1.1, U$2.1 (SDA)
VDD3V3: C1.1, C2.1, JP1.2, R1.2, R2.2, R3.2, U$2.11 (VDDP), U$2.12 (VDD)

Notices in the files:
eagle/Nanopore Amp/CurrentAmp.brd:
Pavlo Manovi - (c) 2014
parts and their libraries:
SparkFun-Aesthetics: Licensing: CC v3.0 Share-Alike You are welcome to use this library for commercial purposes.
